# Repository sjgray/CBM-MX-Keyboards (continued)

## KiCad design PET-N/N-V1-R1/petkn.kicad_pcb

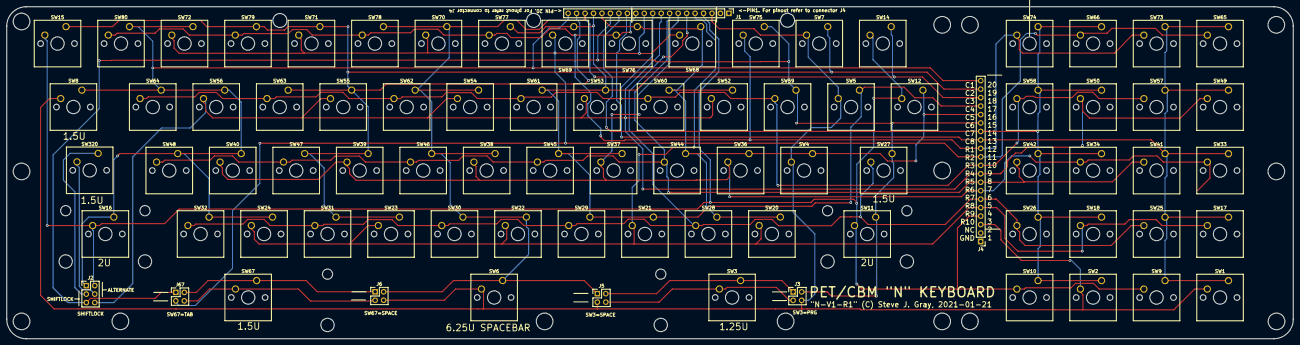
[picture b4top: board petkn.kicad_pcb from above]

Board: 2 copper layers, 386.1 x 99.6 mm, 83 parts (0 on the bottom side), 24 nets.

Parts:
J1, J4: Conn_01x20; PinHeader_1x20_P2.54mm_Vertical
J2: Conn_02x03_Odd_Even; PinHeader_2x03_P2.54mm_Vertical
J3: LINK3; PinHeader_2x02_P2.54mm_Vertical
J5: SPACE1; PinHeader_2x02_P2.54mm_Vertical
J6: SPACE2; PinHeader_2x02_P2.54mm_Vertical
J67: LINK67; PinHeader_2x02_P2.54mm_Vertical
SW1: KP "="; SW_Cherry_MX_1.00u_PCB
SW2: KP "."; SW_Cherry_MX_1.00u_PCB
SW3: NC ($10); SW_Cherry_MX1A_1.25u_PCB
SW4: STOP; SW_Cherry_MX_1.00u_PCB
SW5: "<"; SW_Cherry_MX_1.00u_PCB
SW6: SPACE; SW_Cherry_MX1A_6.25u_PCB
SW7: "["; SW_Cherry_MX_1.00u_PCB
SW8: OFF/RVS; SW_Cherry_MX1A_1.50u_PCB
SW9: KP "-"; SW_Cherry_MX_1.00u_PCB
SW10: KP "0"; SW_Cherry_MX_1.00u_PCB
SW11: R SHIFT; SW_Cherry_MX_2.00u_PCB
SW12: ">"; SW_Cherry_MX_1.00u_PCB
SW14: "]"; SW_Cherry_MX_1.00u_PCB
SW15: "@"; SW_Cherry_MX_1.00u_PCB
SW16: L SHIFT; SW_Cherry_MX_2.00u_PCB
SW17: KP "+"; SW_Cherry_MX_1.00u_PCB
SW18: KP "2"; SW_Cherry_MX_1.00u_PCB
SW20: "?"; SW_Cherry_MX_1.00u_PCB
SW21: ","; SW_Cherry_MX_1.00u_PCB
SW22: "N"; SW_Cherry_MX_1.00u_PCB
SW23: "V"; SW_Cherry_MX_1.00u_PCB
SW24: "X"; SW_Cherry_MX_1.00u_PCB
SW25: KP "3"; SW_Cherry_MX_1.00u_PCB
SW26: KP "1"; SW_Cherry_MX_1.00u_PCB
SW27: RETURN; SW_Cherry_MX1A_1.50u_PCB
SW28: ";"; SW_Cherry_MX_1.00u_PCB
SW29: "M"; SW_Cherry_MX_1.00u_PCB
SW30: "B"; SW_Cherry_MX_1.00u_PCB
SW31: "C"; SW_Cherry_MX_1.00u_PCB
SW32: "Z"; SW_Cherry_MX_1.00u_PCB
SW33: KP "*"; SW_Cherry_MX_1.00u_PCB
SW34: KP "5"; SW_Cherry_MX_1.00u_PCB
SW36: ":"; SW_Cherry_MX_1.00u_PCB
SW37: "K"; SW_Cherry_MX_1.00u_PCB
SW38: "H"; SW_Cherry_MX_1.00u_PCB
SW39: "F"; SW_Cherry_MX_1.00u_PCB
SW40: "S"; SW_Cherry_MX_1.00u_PCB
SW41: KP "6"; SW_Cherry_MX_1.00u_PCB
SW42: KP "4"; SW_Cherry_MX_1.00u_PCB
SW44: "L"; SW_Cherry_MX_1.00u_PCB
SW45: "J"; SW_Cherry_MX_1.00u_PCB
SW46: "G"; SW_Cherry_MX_1.00u_PCB
SW47: "D"; SW_Cherry_MX_1.00u_PCB
SW48: "A"; SW_Cherry_MX_1.00u_PCB
SW49: KP "/"; SW_Cherry_MX_1.00u_PCB
SW50: KP "8"; SW_Cherry_MX_1.00u_PCB
SW52: "P"; SW_Cherry_MX_1.00u_PCB
SW53: "I"; SW_Cherry_MX_1.00u_PCB
SW54: "Y"; SW_Cherry_MX_1.00u_PCB
SW55: "R"; SW_Cherry_MX_1.00u_PCB
SW56: "W"; SW_Cherry_MX_1.00u_PCB
SW57: KP "9"; SW_Cherry_MX_1.00u_PCB
SW58: KP "7"; SW_Cherry_MX_1.00u_PCB
SW59: U ARROW; SW_Cherry_MX_1.00u_PCB
SW60: "O"; SW_Cherry_MX_1.00u_PCB
SW61: "U"; SW_Cherry_MX_1.00u_PCB
SW62: "T"; SW_Cherry_MX_1.00u_PCB
SW63: "E"; SW_Cherry_MX_1.00u_PCB
SW64: "Q"; SW_Cherry_MX_1.00u_PCB
SW65: INS/DEL; SW_Cherry_MX_1.00u_PCB
SW66: UP/DOWN; SW_Cherry_MX_1.00u_PCB
SW67: NC ($0A); SW_Cherry_MX_1.50u_PCB
SW68: ")"; SW_Cherry_MX_1.00u_PCB
SW69: "\"; SW_Cherry_MX_1.00u_PCB
SW70: "'"; SW_Cherry_MX_1.00u_PCB
SW71: "$"; SW_Cherry_MX_1.00u_PCB
SW72: QUOTE; SW_Cherry_MX_1.00u_PCB
SW73: LEFT/RIGHT; SW_Cherry_MX_1.00u_PCB
SW74: CLR/HOME; SW_Cherry_MX_1.00u_PCB
SW75: B ARROW; SW_Cherry_MX_1.00u_PCB
SW76: "("; SW_Cherry_MX_1.00u_PCB
SW77: "&"; SW_Cherry_MX_1.00u_PCB
SW78: "%"; SW_Cherry_MX_1.00u_PCB
SW79: "#"; SW_Cherry_MX_1.00u_PCB
SW80: "!"; SW_Cherry_MX_1.00u_PCB
SW320: S LOCK; SW_Cherry_MX1A_1.50u_PCB

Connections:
C1: J1.20, J2.1, J4.20, SW8.1, SW16.1, SW24.1, SW32.1, SW40.1, SW48.1, SW56.1, SW64.1, SW72.1, SW80.1
C2: J1.19, J4.19, SW7.1, SW15.1, SW23.1, SW31.1, SW39.1, SW47.1, SW55.1, SW63.1, SW71.1, SW79.1
C3: J1.18, J4.18, J5.1, J6.2, SW6.1, SW14.1, SW22.1, SW30.1, SW38.1, SW46.1, SW54.1, SW62.1, SW70.1, SW78.1
C4: J1.17, J4.17, SW5.1, SW21.1, SW29.1, SW37.1, SW45.1, SW53.1, SW61.1, SW69.1, SW77.1
C5: J1.16, J4.16, SW4.1, SW12.1, SW20.1, SW28.1, SW36.1, SW44.1, SW52.1, SW60.1, SW68.1, SW76.1
C6: J1.15, J2.5, J3.2, J4.15, J67.1, SW11.1, SW27.1, SW59.1, SW75.1
C7: J1.14, J4.14, SW2.1, SW10.1, SW18.1, SW26.1, SW34.1, SW42.1, SW50.1, SW58.1, SW66.1, SW74.1
C8: J1.13, J4.13, SW1.1, SW9.1, SW17.1, SW25.1, SW33.1, SW41.1, SW49.1, SW57.1, SW65.1, SW73.1
R1: J1.12, J4.12, SW73.2, SW74.2, SW75.2, SW76.2, SW77.2, SW78.2, SW79.2, SW80.2
R2: J1.11, J4.11, J67.3, SW65.2, SW66.2, SW68.2, SW69.2, SW70.2, SW71.2, SW72.2
R3: J1.10, J4.10, SW57.2, SW58.2, SW59.2, SW60.2, SW61.2, SW62.2, SW63.2, SW64.2
R4: J1.9, J2.6, J4.9, SW49.2, SW50.2, SW52.2, SW53.2, SW54.2, SW55.2, SW56.2
R5: J1.8, J4.8, SW41.2, SW42.2, SW44.2, SW45.2, SW46.2, SW47.2, SW48.2
R6: J1.7, J4.7, SW33.2, SW34.2, SW36.2, SW37.2, SW38.2, SW39.2, SW40.2
R7: J1.6, J4.6, SW25.2, SW26.2, SW27.2, SW28.2, SW29.2, SW30.2, SW31.2, SW32.2
R8: J1.5, J4.5, SW17.2, SW18.2, SW20.2, SW21.2, SW22.2, SW23.2, SW24.2
R9: J1.4, J2.2, J4.4, SW9.2, SW10.2, SW11.2, SW12.2, SW14.2, SW15.2, SW16.2
R10: J1.3, J3.4, J4.3, J5.3, J6.4, SW1.2, SW2.2, SW4.2, SW5.2, SW6.2, SW7.2, SW8.2
XC1: J2.3, SW320.1
XC3: J3.1, J5.2, SW3.1
XC67: J6.1, J67.2, SW67.1
XR1: J2.4, SW320.2
XR3: J3.3, J5.4, SW3.2
XR67: J6.3, J67.4, SW67.2

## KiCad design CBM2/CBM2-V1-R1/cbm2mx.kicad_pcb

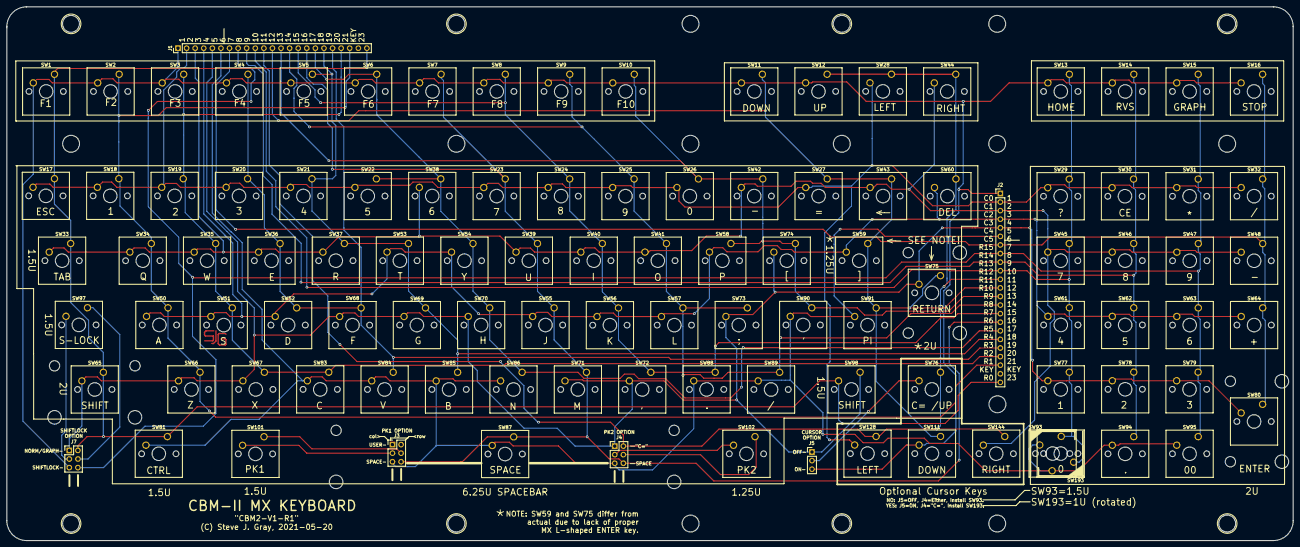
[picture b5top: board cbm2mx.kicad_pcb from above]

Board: 2 copper layers, 380.5 x 157.9 mm, 106 parts (0 on the bottom side), 29 nets.

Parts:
J1, J2: Conn_01x23; PinHeader_1x23_P2.54mm_Vertical
J3: PK1; PinHeader_2x03_P2.54mm_Vertical
J4: PK2; PinHeader_2x03_P2.54mm_Vertical
J5: C=/UP; PinHeader_1x03_P2.54mm_Vertical
J7: S-LOCK OPT; PinHeader_2x03_P2.54mm_Vertical
SW1: "F1"; SW_Cherry_MX_1.00u_PCB
SW2: "F2"; SW_Cherry_MX_1.00u_PCB
SW3: "F3"; SW_Cherry_MX_1.00u_PCB
SW4: "F4"; SW_Cherry_MX_1.00u_PCB
SW5: "F5"; SW_Cherry_MX_1.00u_PCB
SW6: "F6"; SW_Cherry_MX_1.00u_PCB
SW7: "F7"; SW_Cherry_MX_1.00u_PCB
SW8: "F8"; SW_Cherry_MX_1.00u_PCB
SW9: "F9"; SW_Cherry_MX_1.00u_PCB
SW10: "F10"; SW_Cherry_MX_1.00u_PCB
SW11, SW111: "DOWN"; SW_Cherry_MX_1.00u_PCB
SW12: "UP"; SW_Cherry_MX_1.00u_PCB
SW13: "HOME"; SW_Cherry_MX_1.00u_PCB
SW14: "RVS"; SW_Cherry_MX_1.00u_PCB
SW15: "GRAPH"; SW_Cherry_MX_1.00u_PCB
SW16: "STOP"; SW_Cherry_MX_1.00u_PCB
SW17: "ESC"; SW_Cherry_MX_1.00u_PCB
SW18: "1"; SW_Cherry_MX_1.00u_PCB
SW19: "2"; SW_Cherry_MX_1.00u_PCB
SW20: "3"; SW_Cherry_MX_1.00u_PCB
SW21: "4"; SW_Cherry_MX_1.00u_PCB
SW22: "5"; SW_Cherry_MX_1.00u_PCB
SW23: "7"; SW_Cherry_MX_1.00u_PCB
SW24: "8"; SW_Cherry_MX_1.00u_PCB
SW25: "9"; SW_Cherry_MX_1.00u_PCB
SW26: "0"; SW_Cherry_MX_1.00u_PCB
SW27: "="; SW_Cherry_MX_1.00u_PCB
SW28, SW128: "LEFT"; SW_Cherry_MX_1.00u_PCB
SW29: KP "?"; SW_Cherry_MX_1.00u_PCB
SW30: KP "CE"; SW_Cherry_MX_1.00u_PCB
SW31: KP "*"; SW_Cherry_MX_1.00u_PCB
SW32: KP "/"; SW_Cherry_MX_1.00u_PCB
SW33: "TAB"; SW_Cherry_MX_1.50u_PCB
SW34: "Q"; SW_Cherry_MX_1.00u_PCB
SW35: "W"; SW_Cherry_MX_1.00u_PCB
SW36: "E"; SW_Cherry_MX_1.00u_PCB
SW37: "R"; SW_Cherry_MX_1.00u_PCB
SW38: "6"; SW_Cherry_MX_1.00u_PCB
SW39: "U"; SW_Cherry_MX_1.00u_PCB
SW40: "I"; SW_Cherry_MX_1.00u_PCB
SW41: "O"; SW_Cherry_MX_1.00u_PCB
SW42: "-"; SW_Cherry_MX_1.00u_PCB
SW43: "B-ARROW"; SW_Cherry_MX_1.00u_PCB
SW44, SW144: "RIGHT"; SW_Cherry_MX_1.00u_PCB
SW45: KP "7"; SW_Cherry_MX_1.00u_PCB
SW46: KP "8"; SW_Cherry_MX_1.00u_PCB
SW47: KP "9"; SW_Cherry_MX_1.00u_PCB
SW48: KP "-"; SW_Cherry_MX_1.00u_PCB
SW50: "A"; SW_Cherry_MX_1.00u_PCB
SW51: "S"; SW_Cherry_MX_1.00u_PCB
SW52: "D"; SW_Cherry_MX_1.00u_PCB
SW53: "T"; SW_Cherry_MX_1.00u_PCB
SW54: "Y"; SW_Cherry_MX_1.00u_PCB
SW55: "J"; SW_Cherry_MX_1.00u_PCB
SW56: "K"; SW_Cherry_MX_1.00u_PCB
SW57: "L"; SW_Cherry_MX_1.00u_PCB
SW58: "P"; SW_Cherry_MX_1.00u_PCB
SW59: "]"; SW_Cherry_MX_1.25u_PCB
SW60: "DEL"; SW_Cherry_MX_1.00u_PCB
SW61: KP "4"; SW_Cherry_MX_1.00u_PCB
SW62: KP "5"; SW_Cherry_MX_1.00u_PCB
SW63: KP "6"; SW_Cherry_MX_1.00u_PCB
SW64: KP "+"; SW_Cherry_MX_1.00u_PCB
SW65: "SHIFT"; SW_Cherry_MX_2.00u_PCB
SW66: "Z"; SW_Cherry_MX_1.00u_PCB
SW67: "X"; SW_Cherry_MX_1.00u_PCB
SW68: "F"; SW_Cherry_MX_1.00u_PCB
SW69: "G"; SW_Cherry_MX_1.00u_PCB
SW70: "H"; SW_Cherry_MX_1.00u_PCB
SW71: "M"; SW_Cherry_MX_1.00u_PCB
SW72: ","; SW_Cherry_MX_1.00u_PCB
SW73: ";"; SW_Cherry_MX_1.00u_PCB
SW74: "["; SW_Cherry_MX_1.00u_PCB
SW75: "RETURN"; SW_Cherry_MX_2.00u_Vertical_PCB
SW76: "C="/"UP"; SW_Cherry_MX_1.00u_PCB
SW77: KP "1"; SW_Cherry_MX_1.00u_PCB
SW78: KP "2"; SW_Cherry_MX_1.00u_PCB
SW79: KP "3"; SW_Cherry_MX_1.00u_PCB
SW80: "ENTER"; SW_Cherry_MX_2.00u_Vertical_PCB
SW81: "CTRL"; SW_Cherry_MX_1.50u_PCB
SW83: "C"; SW_Cherry_MX_1.00u_PCB
SW84: "V"; SW_Cherry_MX_1.00u_PCB
SW85: "B"; SW_Cherry_MX_1.00u_PCB
SW86: "N"; SW_Cherry_MX_1.00u_PCB
SW87: "SPACE"; SW_Cherry_MX_6.25u_PCB
SW88: "."; SW_Cherry_MX_1.00u_PCB
SW89: "/"; SW_Cherry_MX_1.00u_PCB
SW90: "'"; SW_Cherry_MX_1.00u_PCB
SW91: "PI"; SW_Cherry_MX_1.00u_PCB
SW93: KP"0" Reg; SW_Cherry_MX1A_1.25u_PCB
SW94: KP "."; SW_Cherry_MX_1.00u_PCB
SW95: KP "00"; SW_Cherry_MX_1.00u_PCB
SW97: S-LOCK; SW_Cherry_MX_1.50u_PCB
SW98: R-SHIFT; SW_Cherry_MX_1.50u_PCB
SW101: PRG1; SW_Cherry_MX1A_1.50u_PCB
SW102: PRG2; SW_Cherry_MX1A_1.25u_PCB
SW193: KP"0" Alternate; SW_Cherry_MX_1.00u_PCB

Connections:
C0: J1.1, J2.1, J5.3, J7.5, SW1.2, SW2.2, SW3.2, SW4.2, SW5.2, SW6.2, SW7.2, SW8.2, SW9.2, SW10.2, SW11.2, SW12.2, SW13.2, SW14.2, SW15.2, SW16.2, SW111.2
C1: J1.2, J2.2, SW17.2, SW18.2, SW19.2, SW20.2, SW21.2, SW22.2, SW23.2, SW24.2, SW25.2, SW26.2, SW27.2, SW28.2, SW29.2, SW30.2, SW31.2, SW32.2, SW128.2
C2: J1.3, J2.3, SW33.2, SW34.2, SW35.2, SW36.2, SW37.2, SW38.2, SW39.2, SW40.2, SW41.2, SW42.2, SW43.2, SW44.2, SW45.2, SW46.2, SW47.2, SW48.2, SW144.2
C3: J1.4, J2.4, SW50.2, SW51.2, SW52.2, SW53.2, SW54.2, SW55.2, SW56.2, SW57.2, SW58.2, SW59.2, SW60.2, SW61.2, SW62.2, SW63.2, SW64.2
C4: J1.5, J2.5, J4.1, J5.1, J7.1, SW65.2, SW66.2, SW67.2, SW68.2, SW69.2, SW70.2, SW71.2, SW72.2, SW73.2, SW74.2, SW75.2, SW77.2, SW78.2, SW79.2, SW80.2, SW98.1
C5: J1.6, J2.6, J3.5, J4.5, SW81.2, SW83.2, SW84.2, SW85.2, SW86.2, SW87.2, SW88.2, SW89.2, SW90.2, SW91.2, SW93.2, SW94.2, SW95.2, SW193.1
CEQC: J5.2, SW76.2
PK1C: J3.3, SW101.2
PK1R: J3.4, SW101.1
PK2C: J4.3, SW102.2
PK2R: J4.4, SW102.1
R0: J1.23, J2.23, J7.2, SW1.1, SW17.1, SW33.1, SW65.1, SW81.1, SW98.2
R1: J1.21, J2.21, SW2.1, SW18.1, SW34.1, SW50.1, SW66.1
R2: J1.20, J2.20, SW3.1, SW19.1, SW35.1, SW51.1, SW67.1, SW83.1
R3: J1.19, J2.19, SW4.1, SW20.1, SW36.1, SW52.1, SW68.1, SW84.1
R4: J1.18, J2.18, SW5.1, SW21.1, SW37.1, SW53.1, SW69.1, SW85.1
R5: J1.17, J2.17, SW6.1, SW22.1, SW38.1, SW54.1, SW70.1, SW86.1
R6: J1.16, J2.16, J3.6, J4.6, SW7.1, SW23.1, SW39.1, SW55.1, SW71.1, SW87.1
R7: J1.15, J2.15, SW8.1, SW24.1, SW40.1, SW56.1, SW72.1, SW88.1
R8: J1.14, J2.14, SW9.1, SW25.1, SW41.1, SW57.1, SW73.1, SW89.1
R9: J1.13, J2.13, SW10.1, SW26.1, SW42.1, SW58.1, SW74.1, SW90.1
R10: J1.12, J2.12, SW11.1, SW27.1, SW43.1, SW59.1, SW75.1, SW91.1, SW111.1
R11: J1.11, J2.11, J4.2, SW12.1, SW28.1, SW44.1, SW60.1, SW76.1, SW128.1, SW144.1
R12: J1.10, J2.10, SW13.1, SW29.1, SW45.1, SW61.1, SW77.1, SW93.1, SW193.2
R13: J1.9, J2.9, SW14.1, SW30.1, SW46.1, SW62.1, SW78.1, SW94.1
R14: J1.8, J2.8, J7.6, SW15.1, SW31.1, SW47.1, SW63.1, SW79.1, SW95.1
R15: J1.7, J2.7, SW16.1, SW32.1, SW48.1, SW64.1, SW80.1
SLOCKC: J7.3, SW97.2
SLOCKR: J7.4, SW97.1

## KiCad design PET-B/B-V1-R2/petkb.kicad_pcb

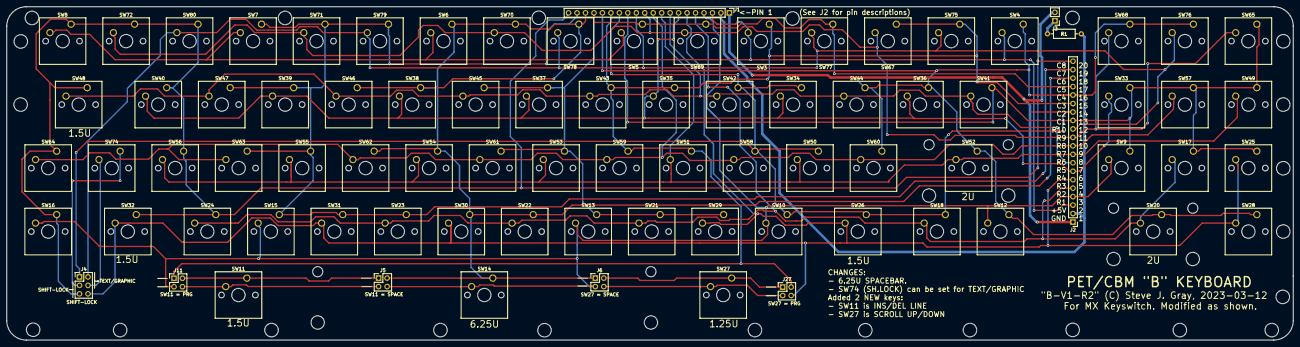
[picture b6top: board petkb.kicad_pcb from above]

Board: 2 copper layers, 386.1 x 100.0 mm, 84 parts (0 on the bottom side), 27 nets.

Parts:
J1, J2: Conn_01x20; PinHeader_1x20_P2.54mm_Vertical
J3: POWER LED; PinHeader_1x02_P2.54mm_Vertical
J4: Conn_02x03_Odd_Even; PinHeader_2x03_P2.54mm_Vertical
J5: SPACE1; PinHeader_2x02_P2.54mm_Vertical
J6: SPACE2; PinHeader_2x02_P2.54mm_Vertical
J11, J27: Conn_02x02_Odd_Even; PinHeader_2x02_P2.54mm_Vertical
R1: R; R_Axial_DIN0207_L6.3mm_D2.5mm_P10.16mm_Horizontal
SW3: ":"; SW_Cherry_MX_1.00u_PCB
SW4: STOP; SW_Cherry_MX_1.00u_PCB
SW5: "9"; SW_Cherry_MX_1.00u_PCB
SW6: "6"; SW_Cherry_MX_1.00u_PCB
SW7: "3"; SW_Cherry_MX_1.00u_PCB
SW8: B ARROW; SW_Cherry_MX_1.00u_PCB
SW9: "KP 1"; SW_Cherry_MX_1.00u_PCB
SW10: "/"; SW_Cherry_MX_1.00u_PCB
SW11: NC $15; SW_Cherry_MX_1.50u_PCB
SW12: HOME; SW_Cherry_MX_1.00u_PCB
SW13: "M"; SW_Cherry_MX_1.00u_PCB
SW14: SPACE; SW_Cherry_MX_6.25u_PCB
SW15: "X"; SW_Cherry_MX_1.00u_PCB
SW16: RVS; SW_Cherry_MX_1.00u_PCB
SW17: "KP 2"; SW_Cherry_MX_1.00u_PCB
SW18: RPT; SW_Cherry_MX_1.00u_PCB
SW20: "0"; SW_Cherry_MX_2.00u_PCB
SW21: ","; SW_Cherry_MX_1.00u_PCB
SW22: "N"; SW_Cherry_MX_1.00u_PCB
SW23: "V"; SW_Cherry_MX_1.00u_PCB
SW24: "Z"; SW_Cherry_MX_1.00u_PCB
SW25: "KP 3"; SW_Cherry_MX_1.00u_PCB
SW26: R SHIFT; SW_Cherry_MX_1.50u_PCB
SW27: NC $19; SW_Cherry_MX_1.25u_PCB
SW28: "KP ."; SW_Cherry_MX_1.00u_PCB
SW29: "."; SW_Cherry_MX_1.00u_PCB
SW30: "B"; SW_Cherry_MX_1.00u_PCB
SW31: "C"; SW_Cherry_MX_1.00u_PCB
SW32: L SHIFT; SW_Cherry_MX_1.50u_PCB
SW33: "KP 4"; SW_Cherry_MX_1.00u_PCB
SW34: "["; SW_Cherry_MX_1.00u_PCB
SW35: "O"; SW_Cherry_MX_1.00u_PCB
SW36: DOWN; SW_Cherry_MX_1.00u_PCB
SW37: "U"; SW_Cherry_MX_1.00u_PCB
SW38: "T"; SW_Cherry_MX_1.00u_PCB
SW39: "E"; SW_Cherry_MX_1.00u_PCB
SW40: "Q"; SW_Cherry_MX_1.00u_PCB
SW41: DEL; SW_Cherry_MX_1.00u_PCB
SW42: "P"; SW_Cherry_MX_1.00u_PCB
SW43: "I"; SW_Cherry_MX_1.00u_PCB
SW44: "\"; SW_Cherry_MX_1.00u_PCB
SW45: "Y"; SW_Cherry_MX_1.00u_PCB
SW46: "R"; SW_Cherry_MX_1.00u_PCB
SW47: "W"; SW_Cherry_MX_1.00u_PCB
SW48: TAB; SW_Cherry_MX_1.50u_PCB
SW49: "KP 6"; SW_Cherry_MX_1.00u_PCB
SW50: "@"; SW_Cherry_MX_1.00u_PCB
SW51: "L"; SW_Cherry_MX_1.00u_PCB
SW52: RETURN; SW_Cherry_MX_2.00u_PCB
SW53: "J"; SW_Cherry_MX_1.00u_PCB
SW54: "G"; SW_Cherry_MX_1.00u_PCB
SW55: "D"; SW_Cherry_MX_1.00u_PCB
SW56: "A"; SW_Cherry_MX_1.00u_PCB
SW57: "KP 5"; SW_Cherry_MX_1.00u_PCB
SW58: ";"; SW_Cherry_MX_1.00u_PCB
SW59: "K"; SW_Cherry_MX_1.00u_PCB
SW60: "]"; SW_Cherry_MX_1.00u_PCB
SW61: "H"; SW_Cherry_MX_1.00u_PCB
SW62: "F"; SW_Cherry_MX_1.00u_PCB
SW63: "S"; SW_Cherry_MX_1.00u_PCB
SW64: ESC; SW_Cherry_MX_1.00u_PCB
SW65: "KP 9"; SW_Cherry_MX_1.00u_PCB
SW67: U ARROW; SW_Cherry_MX_1.00u_PCB
SW68: "KP 7"; SW_Cherry_MX_1.00u_PCB
SW69: "0"; SW_Cherry_MX_1.00u_PCB
SW70: "7"; SW_Cherry_MX_1.00u_PCB
SW71: "4"; SW_Cherry_MX_1.00u_PCB
SW72: "1"; SW_Cherry_MX_1.00u_PCB
SW74: NC $0E; SW_Cherry_MX_1.00u_PCB
SW75: RIGHT; SW_Cherry_MX_1.00u_PCB
SW76: "KP 8"; SW_Cherry_MX_1.00u_PCB
SW77: "-"; SW_Cherry_MX_1.00u_PCB
SW78: "8"; SW_Cherry_MX_1.00u_PCB
SW79: "5"; SW_Cherry_MX_1.00u_PCB
SW80: "2"; SW_Cherry_MX_1.00u_PCB

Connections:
5V: J1.2, J2.2, R1.2
C1: J1.13, J2.13, SW9.1, SW17.1, SW25.1, SW33.1, SW41.1, SW49.1, SW57.1, SW65.1
C2: J1.14, J2.14, J4.1, SW10.1, SW18.1, SW26.1, SW34.1, SW42.1, SW50.1, SW58.1
C3: J1.15, J2.15, J11.1, J27.2, SW3.1, SW35.1, SW43.1, SW51.1, SW59.1, SW67.1, SW75.1
C4: J1.16, J2.16, SW4.1, SW12.1, SW20.1, SW28.1, SW36.1, SW44.1, SW52.1, SW60.1, SW68.1, SW76.1
C5: J1.17, J2.17, SW5.1, SW13.1, SW21.1, SW29.1, SW37.1, SW45.1, SW53.1, SW61.1, SW69.1, SW77.1
C6: J1.18, J2.18, J5.2, J6.1, SW6.1, SW14.1, SW22.1, SW30.1, SW38.1, SW46.1, SW54.1, SW62.1, SW70.1, SW78.1
C7: J1.19, J2.19, SW7.1, SW15.1, SW23.1, SW31.1, SW39.1, SW47.1, SW55.1, SW63.1, SW71.1, SW79.1
C8: J1.20, J2.20, J4.5, SW8.1, SW16.1, SW24.1, SW32.1, SW40.1, SW48.1, SW56.1, SW64.1, SW72.1, SW80.1
GND: J1.1, J2.1, J3.2
unnamed: J3.1, R1.1
R1: J1.3, J2.3, SW3.2, SW4.2, SW5.2, SW6.2, SW7.2, SW8.2
R2: J1.4, J2.4, J5.4, J6.3, J11.3, SW9.2, SW10.2, SW12.2, SW13.2, SW14.2, SW15.2, SW16.2
R3: J1.5, J2.5, SW17.2, SW18.2, SW20.2, SW21.2, SW22.2, SW23.2, SW24.2
R4: J1.6, J2.6, J4.6, J27.4, SW25.2, SW26.2, SW28.2, SW29.2, SW30.2, SW31.2, SW32.2
R5: J1.7, J2.7, SW33.2, SW34.2, SW35.2, SW36.2, SW37.2, SW38.2, SW39.2, SW40.2
R6: J1.8, J2.8, SW41.2, SW42.2, SW43.2, SW44.2, SW45.2, SW46.2, SW47.2, SW48.2
R7: J1.9, J2.9, SW49.2, SW50.2, SW51.2, SW52.2, SW53.2, SW54.2, SW55.2, SW56.2
R8: J1.10, J2.10, SW57.2, SW58.2, SW59.2, SW60.2, SW61.2, SW62.2, SW63.2, SW64.2
R9: J1.11, J2.11, SW65.2, SW67.2, SW68.2, SW69.2, SW70.2, SW71.2, SW72.2
R10: J1.12, J2.12, J4.2, SW75.2, SW76.2, SW77.2, SW78.2, SW79.2, SW80.2
XC1: J4.3, SW74.1
XC2: J5.1, J11.2, SW11.1
XC3: J6.2, J27.1, SW27.1
XR1: J4.4, SW74.2
XR2: J5.3, J11.4, SW11.2
XR3: J6.4, J27.3, SW27.2

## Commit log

2020-12-22 :octocat: Added .gitattributes & .gitignore files
2020-12-22 Initial Release
    B-V1-R1 complete
    N-V1-R1 pcb ordered
2021-01-22 N-V1-R1 spacing fix.
    Gerber directory renamed. Do not use gerbers! Fix to PCB spacing.
    Should be ok, but no gerbers or pcb yet. use at own risk! Do not use the
    gerbers in the error directory unless you just need a keyboard and wont
    be installing it in a case!
2021-02-10 Add sticker sheet, update readme
    This sticker sheet has labelling for both N and B keyboards since most
    keys are common to both. Also includes some alternate key labels.
2021-04-01 Release N-V1-R2
    Full Kicad files and Gerbers
2021-04-01 Update N-V1-R2 schematic
    Updated schematic to remove unused switches, and replace with some more
    descriptive text to make alternate configurations clearer/
2021-04-12 Add N/B Sticker sheets for Black keys
    White on Black, combined.
2021-06-20 CBM2-V1-R1
    Add CBM-II Keyboard, V1-R1. This design is complete,. The PCB mounts
    directly to the case and all keys are functional. It uses a 6.25U
    spacebar.
2023-03-21 B-V1-R2 Release
    B-V1-R2 design complete and tested good. Includes Kicad 7 design files and gerbers. Boards were sent to JLCPCB.
2023-03-21 B-V1-R2 Update readme
    Updated readme to add B-V1-R2.
2023-09-30 Add updated stickers
    Add PET N/B stickers with front graphic symbols. New layout.
2023-10-02 Add CBM-II sticker sheets.
    Add black and whicte CBM-II sticker sheets including graphics symbols.
2023-10-02 Add keycap scans
    Scans of keyboards on flatbed scanner. Most at 150dpi. Used to create sticker sheets and vector files for MaxKeyboard.com
2023-10-02 Update readme.txt
    Add additional version and revision information, and CSX keyboard.
2023-10-03 Add C16 scan
    Add C16 scan
2024-02-25 Folder Re-Org
    Adding root folders for each machine, with subfolders for revisions.
2024-02-26 Add C128SX - CSX-V1-R1
    This is the C128SX customizable keyboard. I have made boards and am currently testing various configurations and options. Check the README for more info.
2024-02-26 V364 Released.
    Tested and working.
2025-11-07 Update README
    Updated webpage link. B-V1-R2 was listed twice. removed old entry. Keyboard is working ok.
2025-11-07 oops, found some typos
    Fix typos
2025-12-05 Add MX-Toggle V1
    MX-Toggle adds locking switch functionality to keyboards using regular MX switches. Usable for my earlier designs. Requires 5Vpower and modification to the PCB. All SMT components for a thin footprin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
2025-12-06 Updated resistor values, BOM
    LED's were too bright. Changed to 1K. Generated new interactive BOM. Add link to Mike's MX-Lock github.
